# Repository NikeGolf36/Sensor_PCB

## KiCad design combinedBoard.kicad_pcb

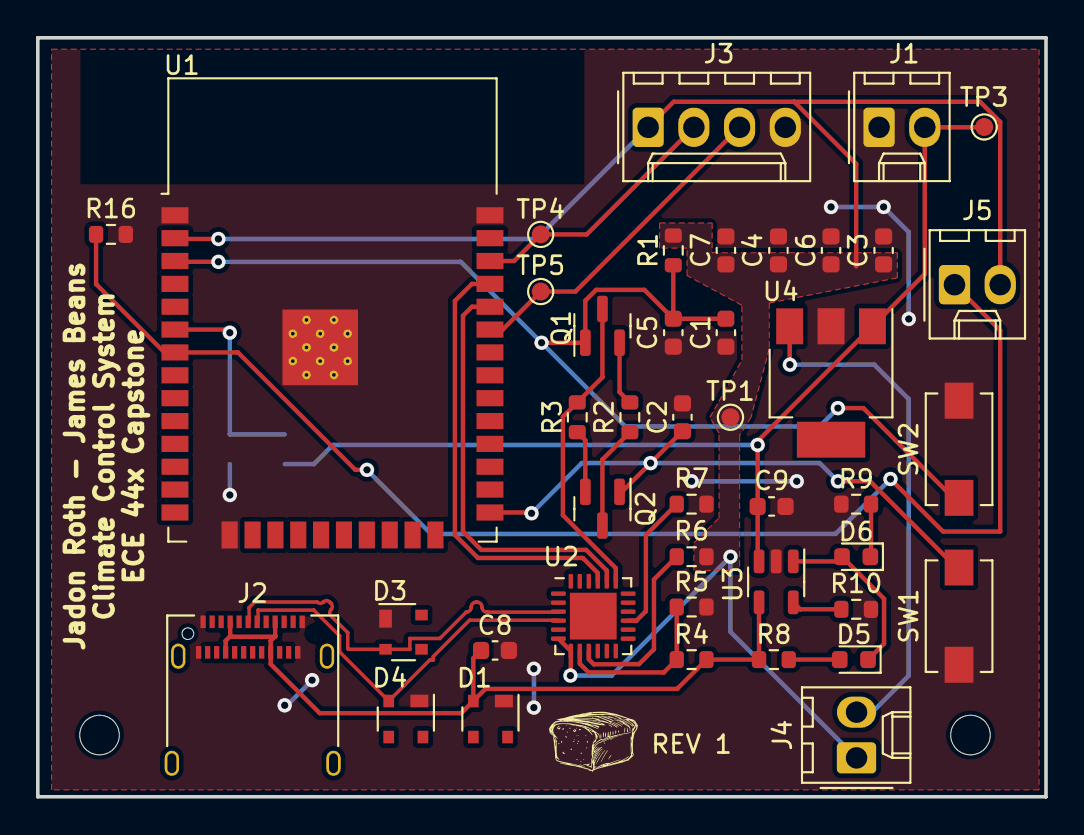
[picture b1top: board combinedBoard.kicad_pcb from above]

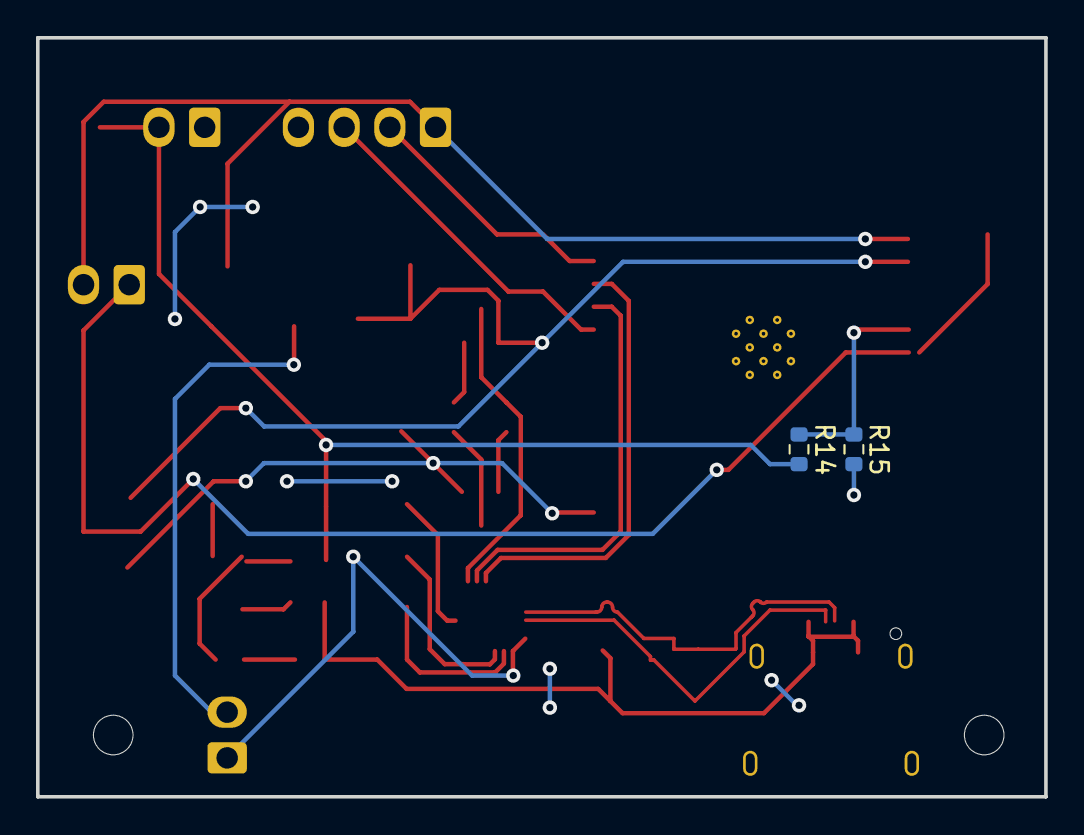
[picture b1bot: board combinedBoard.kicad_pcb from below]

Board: 2 copper layers, 56.0 x 42.2 mm, 46 parts (2 on the bottom side), 26 nets.

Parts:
C1, C2, C4, C5, C7: 0.1uF; C_0603_1608Metric
C3: 22uF; C_0603_1608Metric
C6: 4.7uF; C_0603_1608Metric
C8, C9: 10uF; C_0603_1608Metric
D1, D3, D4: D_TVS; SOT-143
D5, D6: LED; LED_0603_1608Metric
H1, H2: MountingHole; MountingHole_2.2mm_M2
J1, J4, J5: Conn_01x02; Molex_KK-254_AE-6410-02A_1x02_P2.54mm_Vertical
J2: USB_C_Receptacle; USB_C_Receptacle_Amphenol_12401610E4-2A
J3: Conn_01x04; Molex_KK-254_AE-6410-04A_1x04_P2.54mm_Vertical
Q1, Q2: Q_NPN_CBE; SOT-23
R1, R2, R3, R7, R16: 10k; R_0603_1608Metric
R4: 22.1k; R_0603_1608Metric
R5: 47.5k; R_0603_1608Metric
R6, R14, R15: 2k; R_0603_1608Metric
R8, R9: 470; R_0603_1608Metric
R10: 2.2k; R_0603_1608Metric
SW1, SW2: SW_Push; SW_SPST_EVQPE1
TP1, TP3, TP4, TP5: TestPoint; TestPoint_Pad_D1.0mm
U1: ESP32-WROOM-32
U2: CP2102N-Axx-xQFN24; QFN-24-1EP_4x4mm_P0.5mm_EP2.6x2.6mm
U3: MCP73831-2-OT; SOT-23-5
U4: TC1262-33; SOT-223

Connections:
3v3: C3.1, C4.1, C6.2, C7.2, J3.1, J4.1, J5.2, R1.1, R6.2, TP1.1, U1.2 (VDD), U2.6 (VDD), U2.7 (VREGIN)
3v3_S: J4.2, U4.3 (VO)
BT: J5.1, R16.1, U1.7 (IO35)
D+: D3.2 (A2), J2.A6 (D+), J2.B6 (D+), U2.3 (D+)
D-: D4.2 (A2), J2.A7 (D-), J2.B7 (D-), U2.4 (D-)
DTR: Q2.3 (E), R2.1
EN: C1.1, C5.2, Q1.1 (C), R1.2, SW2.2, U1.3 (EN)
GND: C1.2, C2.1, C3.2, C4.2, C5.1, C6.1, C7.1, C8.2, C9.2, D1.1 (A1), D3.1 (A1), D4.1 (A1), J1.1, J2.A1 (GND), J2.A12 (GND), J2.B1 (GND), J2.B12 (GND), J3.4, R5.2, R7.2, R9.1, R10.2, R15.1, R16.2, SW1.1, SW2.1, U1.1 (GND), U1.15 (GND), U1.38 (GND), U1.39 (GND), U2.2 (GND), U3.2 (VSS), U4.2 (GND)
unnamed: D5.1 (K), D6.2 (A), U3.1 (STAT)
unnamed: D5.2 (A), R8.2
unnamed: D6.1 (K), R9.2
unnamed: Q1.2 (B), R2.2
unnamed: Q2.2 (B), R3.2
unnamed: R4.2, R5.1, U2.8 (VBUS)
unnamed: R6.1, U2.9 (~RST)
unnamed: R7.1, U2.15 (~SUSPEND)
unnamed: R10.1, U3.5 (PROG)
unnamed: R14.1, R15.2, U1.6 (IO34)
RESET: C2.2, Q2.1 (C), SW1.2, U1.25 (IO0)
RTS: Q1.3 (E), R3.1, U2.19 (~RTS)
RXD: U1.34 (RXD0/IO3), U2.20 (RXD)
SCL: J3.2, TP4.1, U1.36 (IO22)
SDA: J3.3, TP5.1, U1.33 (IO21)
TXD: U1.35 (TXD0/IO1), U2.21 (TXD)
Vbat: C9.1, J1.2, R14.2, TP3.1, U3.3 (VBAT), U4.1 (VI)
Vbus: C8.1, D1.2 (A2), J2.A4 (VBUS), J2.A9 (VBUS), J2.B4 (VBUS), J2.B9 (VBUS), R4.1, R8.1, U3.4 (VDD)

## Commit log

2023-04-21 Init
